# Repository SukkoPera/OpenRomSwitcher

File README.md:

# OpenRomSwitcher
OpenRomSwitcher is an Open Hardware adapter PCB that allows the use of a 27xxx EPROM in place of a smaller (E)PROM. This is useful, for instance, for replacing the KERNAL and other ROMs in Commodore 16 home computers.

### Summary
When installing [JiffyDOS](http://www.go4retro.com/products/jiffydos/) on a Commodore 16, you might want to retain the ability of switching to the original KERNAL ROM. The C16 ROM pinout is the same as a 27128 EPROM, so you can use a 27256 and put both the JiffyDOS and the original KERNAL on it. To you switch between them, you will need to either connect the A14 pin to VCC or GND.

OpenRomSwitcher comes as an adapter PCB that sits inbetween the original socket and the new chip and carries the A13-A15 pins out to solder pads where switches can be wired to allow the selection of a particular ROM.

### Assembly
1. Solder the 0805 SMD resistors first. My suggested technique is as follows: put a small blob of solder on one of the pads, then grab a resistor with tweezers, reheat the solder and slide the resistor into it, keeping it flat on the board. Hold it in place with your tweezers and take the iron away. If you didn't place it straight, reheat and correct with the tweezers. Finally solder the other end. It's not that hard, you just need to practice a few times.
1. Put the pin headers into a solderless breadboard and lay the board on them, with the 0805 resistors facing down (i.e.: you should not see them). Make sure to use the two shortest hole series. Solder into place.
1. Remove the board from the solderless breadboard. Using flush cutters, cut the top two pins on the right (on the soldering side) so that they are as flush to the board as possible. Repeat with the bottom two pins. Take the socket and do a test fit, it should sit flush to the board.
1. Turn the board over and solder down the socket. Again, make sure it sits as flush as possible.
1. You are done! Try to fit the adapter in the socket on your board or solder it down, if you prefer. In both cases, you can trim the pins shorter if you need.

### Installation
Care is needed to select the proper values and placement of the resistors. You will have to choose on your own, depending on the EPROM, number of switches and exact pin connection of the original socket. Only one resistor must be soldered for each of the A13-A15 pins, either in the *Switch* or *Straight* position. This means **you will ALWAYS need EXACTLY 3 resistors**:

* In case you want to connect an address pin straight to the original socket, solder a 0 ohm resistor in the *Straight* position.
* In case you want to make an address pin switchable, solder a 10 kohm resistor to the *Switch* position. Note that probably any value between 5k and 50k will do.

OpenRomSwitcher has been kept as small as pratically possible, and thus it can usually be installed in the original ROM socket, with no need to desolder it.

To switch between ROMs, you will need one or more switches. Every switch must connect one of the A13-A15 pads to ground when enabled. A ground pad is available on the board, but any ground spot on the original board can be used as well, if easier to reach. Since having more than switch can be cumbersome, a rotary switch can be used as well.

**IMPORTANT: ALWAYS TURN YOUR DEVICE OFF BEFORE MOVING THE ROM SELECTION SWITCH(ES).**

### Example
Reconsidering the initial example of a 27256 EEPROM in the C16, I would use the following resistors:

* A13: A 0 ohm resistor in the *Straight* position, since C16 ROMs are 16 KB and thus the A13 line must be connected to the chip.
* A14: A 10 kohm resistor in the *Switch* position.
* A15: A 0 ohm resistor in the *Straight* position, since both 27128 and 27256 ROMs do not have an A15 pin and we can just connect that pin straight.

With this configuration a switch on the A14 pad that will allow switching between the ROMs.

### License
OpenRomSwitcher is Open Hardware.

### Thanks
The following links were useful during the development of this project:
- https://ist.uwaterloo.ca/~schepers/roms.html
- https://ist.uwaterloo.ca/~schepers/sockets.html

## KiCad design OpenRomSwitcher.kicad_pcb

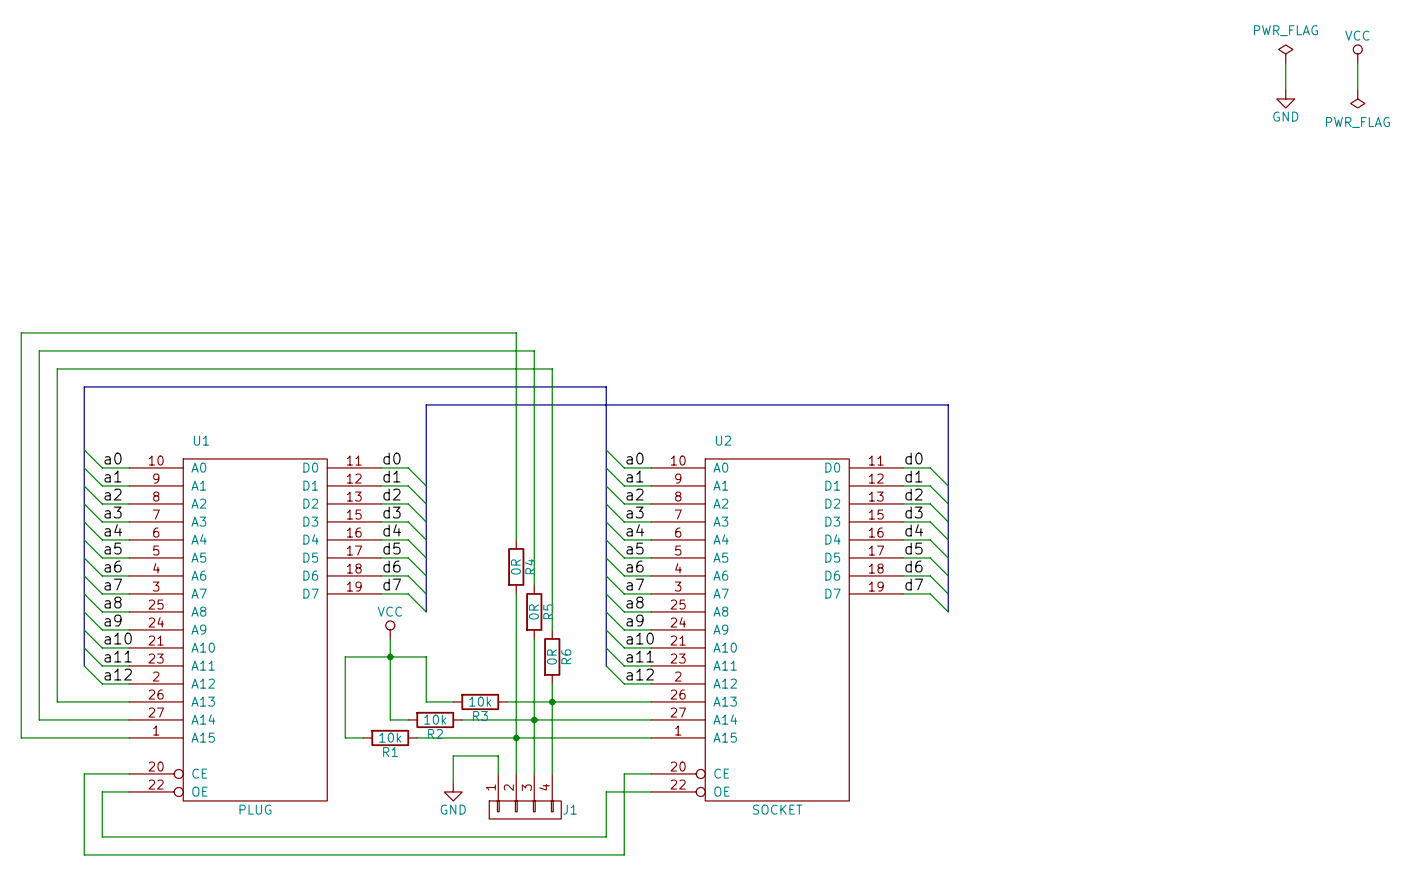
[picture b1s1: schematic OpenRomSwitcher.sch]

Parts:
J1: CONN_01X04; LoosePads-4
R1, R2, R3: 10k; R_0805_HandSoldering
R4, R5, R6: 0R; R_0805_HandSoldering
U1: PLUG; DIP-28_W15.24mm-NoSilkS
U2: SOCKET; DIP-28_W15.24mm-Notch

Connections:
/a0: U1.10 (A0), U2.10 (A0)
/a1: U1.9 (A1), U2.9 (A1)
/a2: U1.8 (A2), U2.8 (A2)
/a3: U1.7 (A3), U2.7 (A3)
/a4: U1.6 (A4), U2.6 (A4)
/a5: U1.5 (A5), U2.5 (A5)
/a6: U1.4 (A6), U2.4 (A6)
/a7: U1.3 (A7), U2.3 (A7)
/a8: U1.25 (A8), U2.25 (A8)
/a9: U1.24 (A9), U2.24 (A9)
/a10: U1.21 (A10), U2.21 (A10)
/a11: U1.23 (A11), U2.23 (A11)
/a12: U1.2 (A12), U2.2 (A12)
/d0: U1.11 (D0), U2.11 (D0)
/d1: U1.12 (D1), U2.12 (D1)
/d2: U1.13 (D2), U2.13 (D2)
/d3: U1.15 (D3), U2.15 (D3)
/d4: U1.16 (D4), U2.16 (D4)
/d5: U1.17 (D5), U2.17 (D5)
/d6: U1.18 (D6), U2.18 (D6)
/d7: U1.19 (D7), U2.19 (D7)
GND: J1.1, U1.14 (GND), U2.14 (GND)
unnamed: J1.2, R1.1, R4.2, U2.1 (A15)
unnamed: J1.3, R2.1, R5.2, U2.27 (A14)
unnamed: J1.4, R3.1, R6.2, U2.26 (A13)
unnamed: R4.1, U1.1 (A15)
unnamed: R5.1, U1.27 (A14)
unnamed: R6.1, U1.26 (A13)
unnamed: U1.20 (CE), U2.20 (CE)
unnamed: U1.22 (OE), U2.22 (OE)
VCC: R1.2, R2.2, R3.2, U1.28 (VCC), U2.28 (VCC)

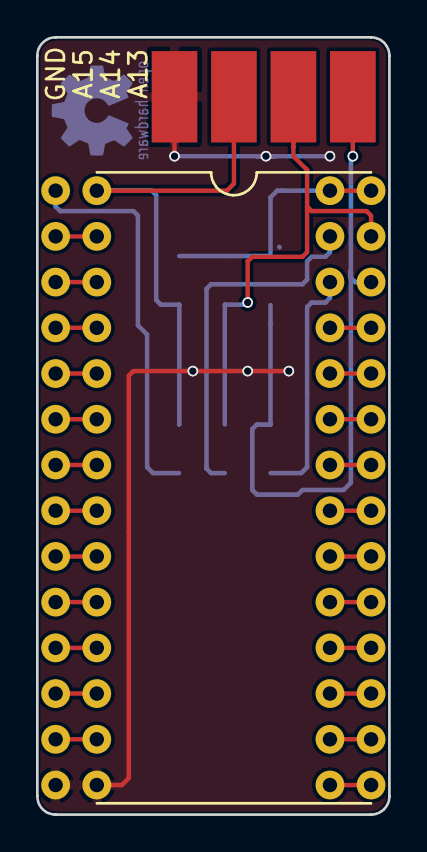
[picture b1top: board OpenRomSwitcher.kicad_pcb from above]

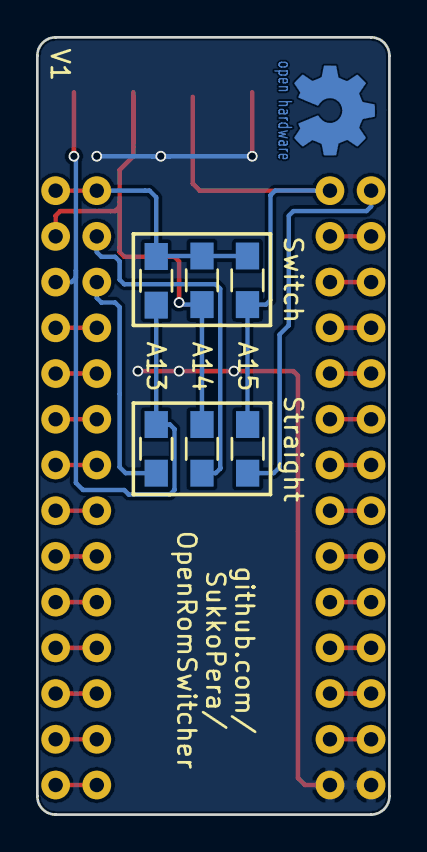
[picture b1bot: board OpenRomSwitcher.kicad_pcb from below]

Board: 2 copper layers, 19.6 x 43.2 mm, 9 parts (6 on the bottom side), 31 nets.

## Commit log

2018-01-07 Final touches for V1
2018-01-07 Add README
2018-01-07 Update README and image
